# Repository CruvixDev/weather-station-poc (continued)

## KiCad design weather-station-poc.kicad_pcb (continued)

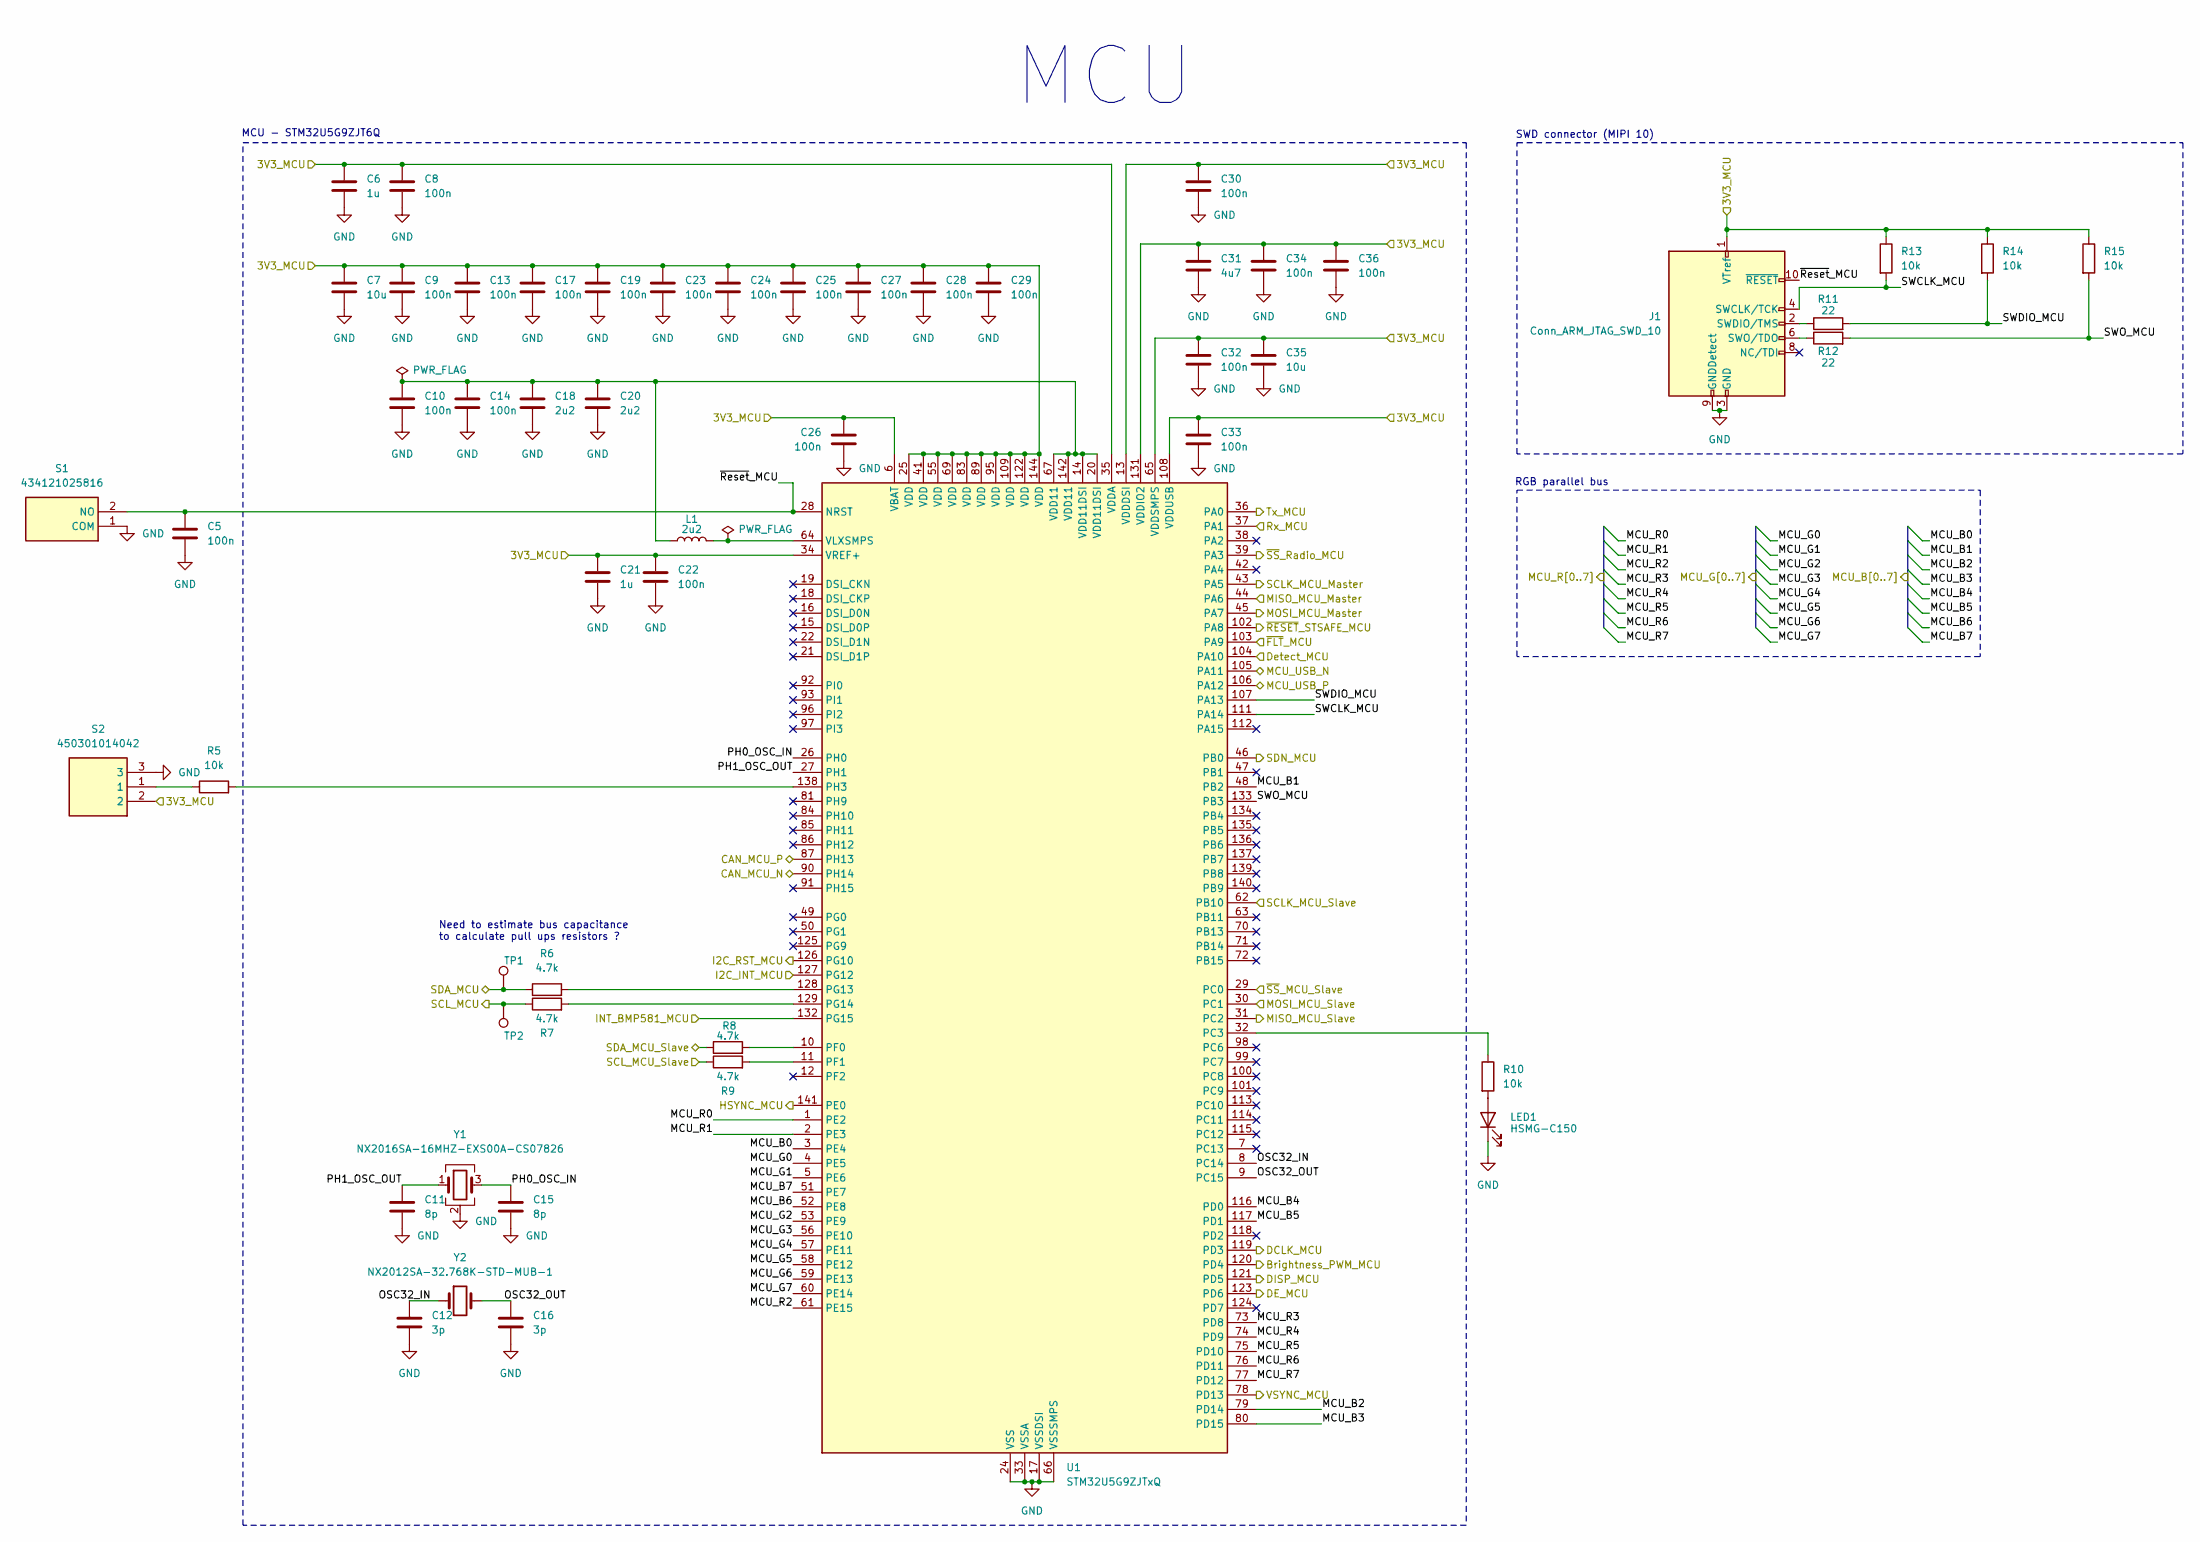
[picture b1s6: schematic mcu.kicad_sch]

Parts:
C5, C8, C9, C10, C13, C14, C17, C19, C22, C23, C24, C25, C26, C27, C28, C29, C30, C32, C33, C34, C36: 100n; C_0603_1608Metric_Pad1.08x0.95mm_HandSolder; Manufacturer_Part_Number 885012206020
C6, C21: 1u; C_0603_1608Metric_Pad1.08x0.95mm_HandSolder; Manufacturer_Part_Number 885012206026
C7, C35: 10u; C_0603_1608Metric_Pad1.08x0.95mm_HandSolder; Manufacturer_Part_Number GRM188Z71A106KA73D
C11, C15: 8p; C_0402_1005Metric_Pad0.74x0.62mm_HandSolder; Manufacturer_Part_Number CC0402CRNPO9BN8R2
C12, C16: 3p; C_0402_1005Metric_Pad0.74x0.62mm_HandSolder; Manufacturer_Part_Number CC0402BRNPO9BN3R3
C18, C20: 2u2; C_0603_1608Metric_Pad1.08x0.95mm_HandSolder; Manufacturer_Part_Number 885012206027
C31: 4u7; C_0603_1608Metric_Pad1.08x0.95mm_HandSolder; Manufacturer_Part_Number GRM188Z71A475KE15J
J1: Conn_ARM_JTAG_SWD_10; FTSH10501LDVK; Manufacturer_Part_Number FTSH-105-01-L-DV-K
L1: 2u2; L_0805_2012Metric_Pad1.05x1.20mm_HandSolder; Manufacturer_Part_Number LQM21PN2R2MGHL
LED1: HSMG-C150; LEDC3216X120N; Mouser Part Number 630-HSMG-C150
R5, R10, R13, R14, R15: 10k; R_0603_1608Metric_Pad0.98x0.95mm_HandSolder; Manufacturer_Part_Number 560112116005
R6, R7, R8, R9: 4.7k; R_0603_1608Metric_Pad0.98x0.95mm_HandSolder; Manufacturer_Part_Number 560112116006
R11, R12: 22; R_0603_1608Metric_Pad0.98x0.95mm_HandSolder; Manufacturer_Part_Number 560112116043
S1: 434121025816; 434121050816; Mouser Part Number 710-434121025816
S2: 450301014042; Mouser Part Number 710-450301014042
TP1, TP2: TestPoint; 5015; Manufacturer_Part_Number N/A
U1: STM32U5G9ZJTxQ; LQFP-144_20x20mm_P0.5mm; Manufacturer_Part_Number STM32U5G9ZJT6Q
Y1: NX2016SA-16MHZ-EXS00A-CS07826; NX2016SA16MHZEXS00ACS07826; Mouser Part Number 344-MHZEXS00ACS07826
Y2: NX2012SA-32.768K-STD-MUB-1; NX2012SA32768KSTDMUB1; Mouser Part Number 344-NX2012SA32768K1

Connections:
+3V3: C6.1, C7.1, C8.1, C9.1, C13.1, C17.1, C19.1, C21.1, C22.1, C23.1, C24.1, C25.1, C26.2, C27.1, C28.1, C29.1, C30.2, C31.1, C32.2, C33.1, C34.1, C35.1, C36.1, J1.1 (VTref), R13.1, R14.1, R15.1, S2.2, U1.6 (VBAT), U1.13 (VDDDSI), U1.25 (VDD), U1.34 (VREF+), U1.35 (VDDA), U1.41 (VDD), U1.55 (VDD), U1.65 (VDDSMPS), U1.69 (VDD), U1.83 (VDD), U1.89 (VDD), U1.95 (VDD), U1.108 (VDDUSB), U1.109 (VDD), U1.122 (VDD), U1.131 (VDDIO2), U1.144 (VDD); also elsewhere on the board
/debug/CAN_Debug_N: U1.90 (PH14); also elsewhere on the board
/debug/CAN_Debug_P: U1.87 (PH13); also elsewhere on the board
/debug/MISO_Debug: U1.31 (PC2); also elsewhere on the board
/debug/MOSI_Debug: U1.30 (PC1); also elsewhere on the board
/debug/Rx_Debug: U1.36 (PA0); also elsewhere on the board
/debug/SCLK_Debug: U1.62 (PB10); also elsewhere on the board
/debug/SCL_Debug: R9.1; also elsewhere on the board
/debug/SDA_Debug: R8.1; also elsewhere on the board
/debug/Tx_Debug: U1.37 (PA1); also elsewhere on the board
/debug/~SS_Debug: U1.29 (PC0); also elsewhere on the board
/lcd/DCLK_LCD: U1.119 (PD3); also elsewhere on the board
/lcd/DE_LCD: U1.123 (PD6); also elsewhere on the board
/lcd/DISP_LCD: U1.121 (PD5); also elsewhere on the board
/lcd/HSYNC_LCD: U1.141 (PE0); also elsewhere on the board
/lcd/I2C_INT_LCD: U1.127 (PG12); also elsewhere on the board
/lcd/I2C_RST_LCD: U1.126 (PG10); also elsewhere on the board
/lcd/LCD_B0: U1.3 (PE4); also elsewhere on the board
/lcd/LCD_B1: U1.48 (PB2); also elsewhere on the board
/lcd/LCD_B2: U1.79 (PD14); also elsewhere on the board
/lcd/LCD_B3: U1.80 (PD15); also elsewhere on the board
/lcd/LCD_B4: U1.116 (PD0); also elsewhere on the board
/lcd/LCD_B5: U1.117 (PD1); also elsewhere on the board
/lcd/LCD_B6: U1.52 (PE8); also elsewhere on the board
/lcd/LCD_B7: U1.51 (PE7); also elsewhere on the board
/lcd/LCD_G0: U1.4 (PE5); also elsewhere on the board
/lcd/LCD_G1: U1.5 (PE6); also elsewhere on the board
/lcd/LCD_G2: U1.53 (PE9); also elsewhere on the board
/lcd/LCD_G3: U1.56 (PE10); also elsewhere on the board
/lcd/LCD_G4: U1.57 (PE11); also elsewhere on the board
/lcd/LCD_G5: U1.58 (PE12); also elsewhere on the board
/lcd/LCD_G6: U1.59 (PE13); also elsewhere on the board
/lcd/LCD_G7: U1.60 (PE14); also elsewhere on the board
/lcd/LCD_R0: U1.1 (PE2); also elsewhere on the board
/lcd/LCD_R1: U1.2 (PE3); also elsewhere on the board
/lcd/LCD_R2: U1.61 (PE15); also elsewhere on the board
/lcd/LCD_R3: U1.73 (PD8); also elsewhere on the board
/lcd/LCD_R4: U1.74 (PD9); also elsewhere on the board
/lcd/LCD_R5: U1.75 (PD10); also elsewhere on the board
/lcd/LCD_R6: U1.76 (PD11); also elsewhere on the board
/lcd/LCD_R7: U1.77 (PD12); also elsewhere on the board
/lcd/SCL_LCD: R7.1, TP2.1 (1_1); also elsewhere on the board
/lcd/SDA_LCD: R6.1, TP1.1 (1_1); also elsewhere on the board
/lcd/VSYNC_LCD: U1.78 (PD13); also elsewhere on the board
/mcu/Brightness_PWM_MCU: U1.120 (PD4); also elsewhere on the board
/mcu/Detect_MCU: U1.104 (PA10); also elsewhere on the board
/mcu/INT_BMP581_MCU: U1.132 (PG15); also elsewhere on the board
/mcu/MCU_USB_N: U1.105 (PA11); also elsewhere on the board
/mcu/MCU_USB_P: U1.106 (PA12); also elsewhere on the board
/mcu/MISO_MCU_Master: U1.44 (PA6); also elsewhere on the board
/mcu/MOSI_MCU_Master: U1.45 (PA7); also elsewhere on the board
/mcu/OSC32_IN: C12.1, U1.8 (PC14), Y2.1
/mcu/OSC32_OUT: C16.1, U1.9 (PC15), Y2.2
/mcu/PH0_OSC_IN: C15.2, U1.26 (PH0), Y1.3
/mcu/PH1_OSC_OUT: C11.2, U1.27 (PH1), Y1.1
/mcu/SCLK_MCU_Master: U1.43 (PA5); also elsewhere on the board
/mcu/SDN_MCU: U1.46 (PB0); also elsewhere on the board
/mcu/SWCLK_MCU: J1.4 (SWCLK/TCK), R13.2, U1.111 (PA14)
/mcu/SWDIO_MCU: R11.2, R14.2, U1.107 (PA13)
/mcu/SWO_MCU: R12.2, R15.2, U1.133 (PB3)
/mcu/~FLT_MCU: U1.103 (PA9); also elsewhere on the board
/mcu/~RESET_STSAFE_MCU: U1.102 (PA8); also elsewhere on the board
/mcu/~Reset_MCU: C5.1, J1.10 (~RESET), S1.2 (NO), U1.28 (NRST)
/mcu/~SS_Radio_MCU: U1.39 (PA3); also elsewhere on the board
GND: C5.2, C6.2, C7.2, C8.2, C9.2, C10.2, C11.1, C12.2, C13.2, C14.2, C15.1, C16.2, C17.2, C18.2, C19.2, C20.2, C21.2, C22.2, C23.2, C24.2, C25.2, C26.1, C27.2, C28.2, C29.2, C30.1, C31.2, C32.1, C33.2, C34.2, C35.2, C36.2, J1.3 (GND), J1.5 (GND), J1.9 (GNDDetect), LED1.1 (K), S1.1 (COM), S2.3, U1.17 (VSSDSI), U1.23 (VSSDSI), U1.24 (VSS), U1.33 (VSSA), U1.40 (VSS), U1.54 (VSS), U1.66 (VSSSMPS), U1.68 (VSS), U1.82 (VSS), U1.88 (VSS), U1.94 (VSS), U1.110 (VSS), U1.130 (VSS), U1.143 (VSS), Y1.2 (G), Y1.4 (G); also elsewhere on the board
unnamed: C10.1, C14.1, C18.1, C20.1, L1.2, U1.14 (VDD11DSI), U1.20 (VDD11DSI), U1.67 (VDD11), U1.142 (VDD11)
unnamed: J1.2 (SWDIO/TMS), R11.1
unnamed: J1.6 (SWO/TDO), R12.1
unnamed: LED1.2 (A), R10.2
unnamed: R5.1, S2.1
unnamed: R10.1, U1.32 (PC3)
unnamed: R8.2, U1.10 (PF0)
unnamed: R9.2, U1.11 (PF1)
unnamed: R6.2, U1.128 (PG13)
unnamed: R7.2, U1.129 (PG14)
unnamed: R5.2, U1.138 (PH3)
unnamed: L1.1, U1.64 (VLXSMPS)

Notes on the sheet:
SWD connector (MIPI 10)
RGB parallel bus
Need to estimate bus capacitance to calculate pull ups resistors ?
MCU - STM32U5G9ZJT6Q
MCU

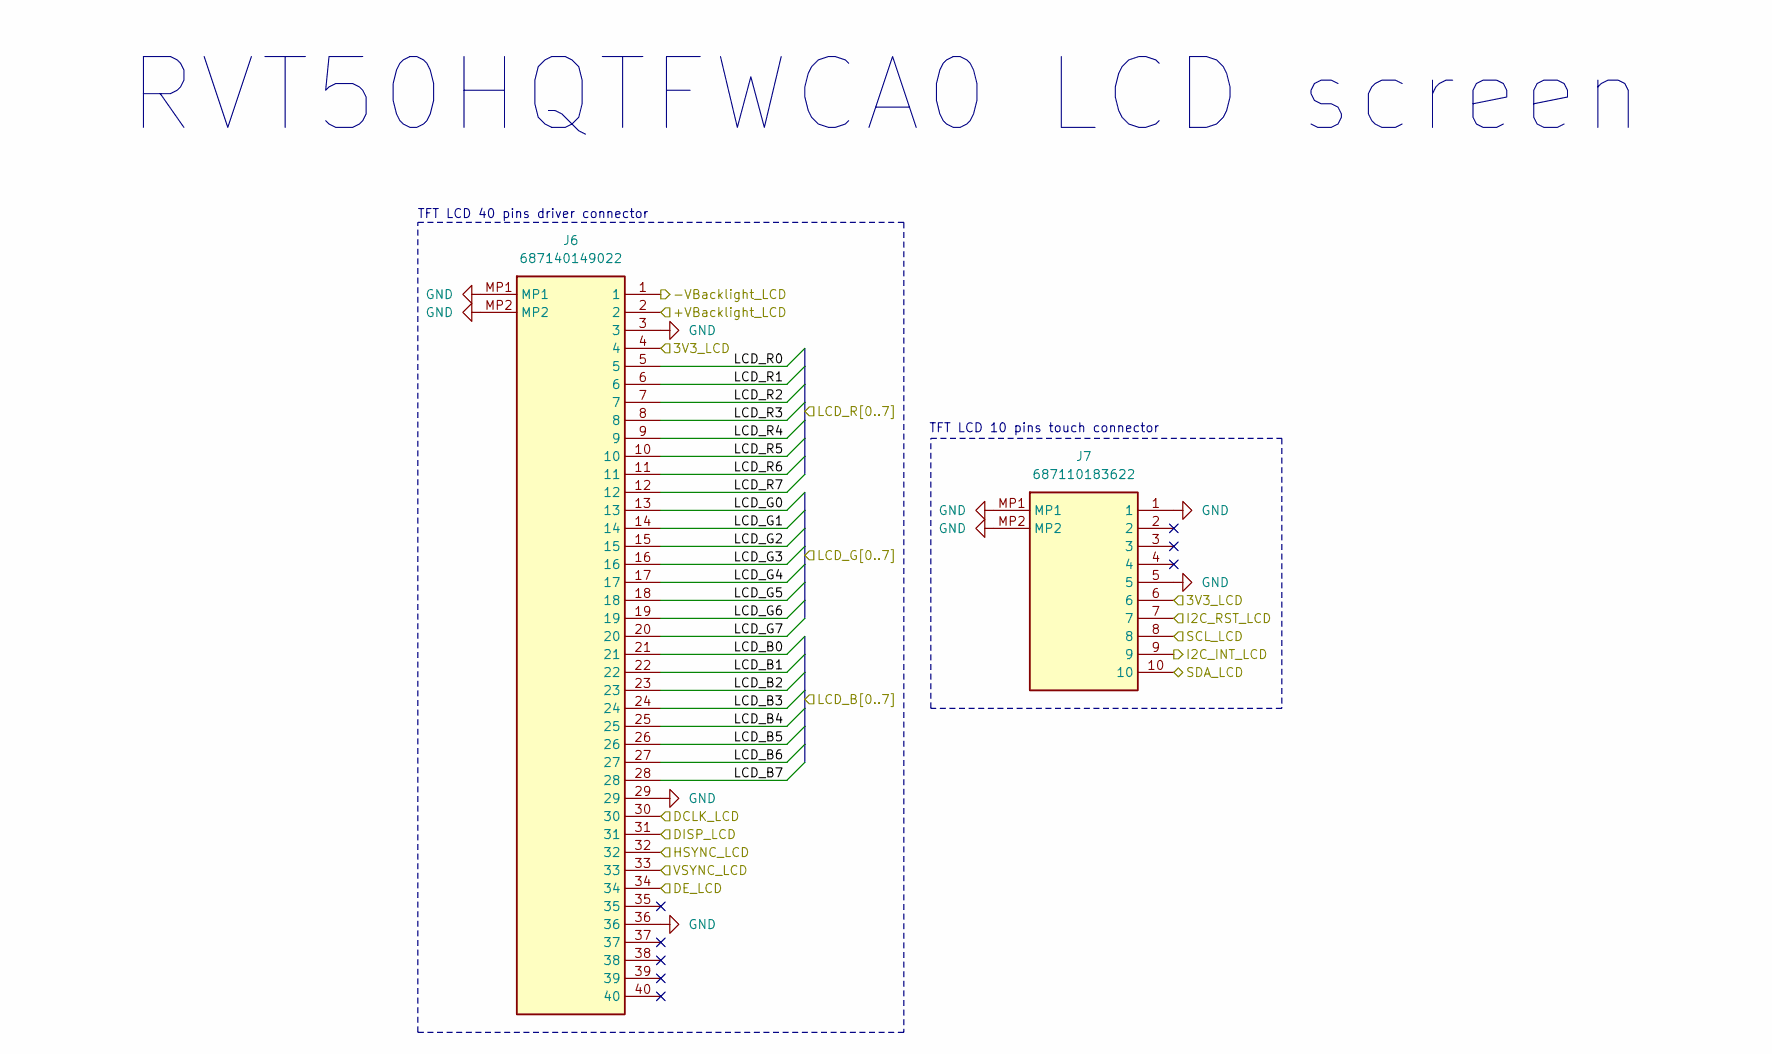
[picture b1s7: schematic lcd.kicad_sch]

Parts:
J6: 687140149022; Mouser Part Number 710-687140149022
J7: 687110183622; Mouser Part Number 710-687110183622

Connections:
+3V3: J6.4, J7.6; also elsewhere on the board
/lcd/+VBacklight_LCD: J6.2; also elsewhere on the board
/lcd/-VBacklight_LCD: J6.1; also elsewhere on the board
/lcd/DCLK_LCD: J6.30; also elsewhere on the board
/lcd/DE_LCD: J6.34; also elsewhere on the board
/lcd/DISP_LCD: J6.31; also elsewhere on the board
/lcd/HSYNC_LCD: J6.32; also elsewhere on the board
/lcd/I2C_INT_LCD: J7.9; also elsewhere on the board
/lcd/I2C_RST_LCD: J7.7; also elsewhere on the board
/lcd/LCD_B0: J6.21; also elsewhere on the board
/lcd/LCD_B1: J6.22; also elsewhere on the board
/lcd/LCD_B2: J6.23; also elsewhere on the board
/lcd/LCD_B3: J6.24; also elsewhere on the board
/lcd/LCD_B4: J6.25; also elsewhere on the board
/lcd/LCD_B5: J6.26; also elsewhere on the board
/lcd/LCD_B6: J6.27; also elsewhere on the board
/lcd/LCD_B7: J6.28; also elsewhere on the board
/lcd/LCD_G0: J6.13; also elsewhere on the board
/lcd/LCD_G1: J6.14; also elsewhere on the board
/lcd/LCD_G2: J6.15; also elsewhere on the board
/lcd/LCD_G3: J6.16; also elsewhere on the board
/lcd/LCD_G4: J6.17; also elsewhere on the board
/lcd/LCD_G5: J6.18; also elsewhere on the board
/lcd/LCD_G6: J6.19; also elsewhere on the board
/lcd/LCD_G7: J6.20; also elsewhere on the board
/lcd/LCD_R0: J6.5; also elsewhere on the board
/lcd/LCD_R1: J6.6; also elsewhere on the board
/lcd/LCD_R2: J6.7; also elsewhere on the board
/lcd/LCD_R3: J6.8; also elsewhere on the board
/lcd/LCD_R4: J6.9; also elsewhere on the board
/lcd/LCD_R5: J6.10; also elsewhere on the board
/lcd/LCD_R6: J6.11; also elsewhere on the board
/lcd/LCD_R7: J6.12; also elsewhere on the board
/lcd/SCL_LCD: J7.8; also elsewhere on the board
/lcd/SDA_LCD: J7.10; also elsewhere on the board
/lcd/VSYNC_LCD: J6.33; also elsewhere on the board
GND: J6.3, J6.29, J6.36, J6.MP1, J6.MP2, J7.1, J7.5, J7.MP1, J7.MP2; also elsewhere on the board

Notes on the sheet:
TFT LCD 40 pins driver connector
TFT LCD 10 pins touch connector
RVT50HQTFWCA0 LCD screen

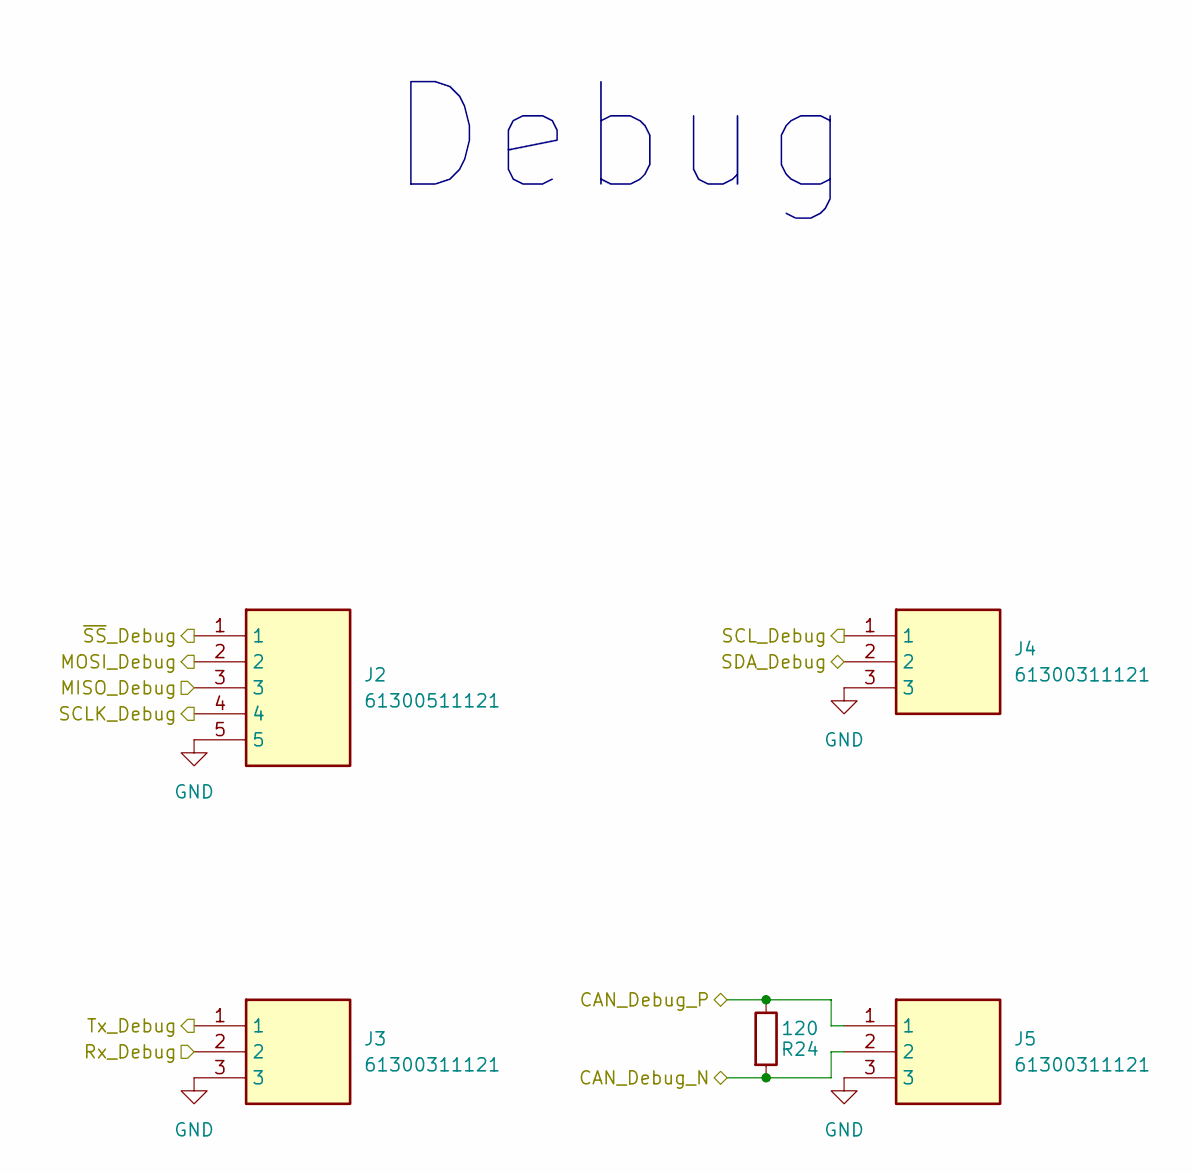
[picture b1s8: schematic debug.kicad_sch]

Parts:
J2: 61300511121; HDRV5W64P0X254_1X5_1270X254X854P; Mouser Part Number 710-61300511121
J3, J4, J5: 61300311121; HDRV3W64P0X254_1X3_762X254X869P; Mouser Part Number 710-61300311121
R24: 120; R_0603_1608Metric_Pad0.98x0.95mm_HandSolder; Manufacturer_Part_Number 560112116092

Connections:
/debug/CAN_Debug_N: J5.2, R24.2; also elsewhere on the board
/debug/CAN_Debug_P: J5.1, R24.1; also elsewhere on the board
/debug/MISO_Debug: J2.3; also elsewhere on the board
/debug/MOSI_Debug: J2.2; also elsewhere on the board
/debug/Rx_Debug: J3.2; also elsewhere on the board
/debug/SCLK_Debug: J2.4; also elsewhere on the board
/debug/SCL_Debug: J4.1; also elsewhere on the board
/debug/SDA_Debug: J4.2; also elsewhere on the board
/debug/Tx_Debug: J3.1; also elsewhere on the board
/debug/~SS_Debug: J2.1; also elsewhere on the board
GND: J2.5, J3.3, J4.3, J5.3; also elsewhere on the board

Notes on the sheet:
Debug

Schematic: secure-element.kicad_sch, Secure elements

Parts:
C78: 10u; C_0603_1608Metric_Pad1.08x0.95mm_HandSolder; Manufacturer_Part_Number GRM188Z71A106KA73D
C79: 100n; C_0603_1608Metric_Pad1.08x0.95mm_HandSolder; Manufacturer_Part_Number 885012206020
IC9: STSAFA110S8OCD03; SOIC127P600X175-8N; Mouser Part Number 511-STSAFA110S8OCD03

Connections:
+3V3: C78.1, C79.1, IC9.2 (VCC); also elsewhere on the board
/lcd/SCL_LCD: IC9.7 (SCL); also elsewhere on the board
/lcd/SDA_LCD: IC9.5 (SDA); also elsewhere on the board
/mcu/~RESET_STSAFE_MCU: IC9.1 (~RESET); also elsewhere on the board
GND: C78.2, C79.2, IC9.4 (GND); also elsewhere on the board

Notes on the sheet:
STSAFE-A110
Secure element (STSAFE)

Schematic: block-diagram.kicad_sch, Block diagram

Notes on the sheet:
JLCPCB stackup
L1 and L4 have a direct return paths through solid ground plane on L2 and L3. But Pwr on L1 is perhaps an issue in terms of EMC ?
3313 FR4 DK = 4.1 So 0.149mm trace width => 50.01 ohms For USB differentials pairs, 0.149mm trace width and 0.163mm spacing => 90.07 ohms (90 ohms +/- 10% for USB) Calculation according PCB way impedance calculator : ( https://www.pcbway.com/pcb_prototype/impedance_calculator.html )
PCB build up

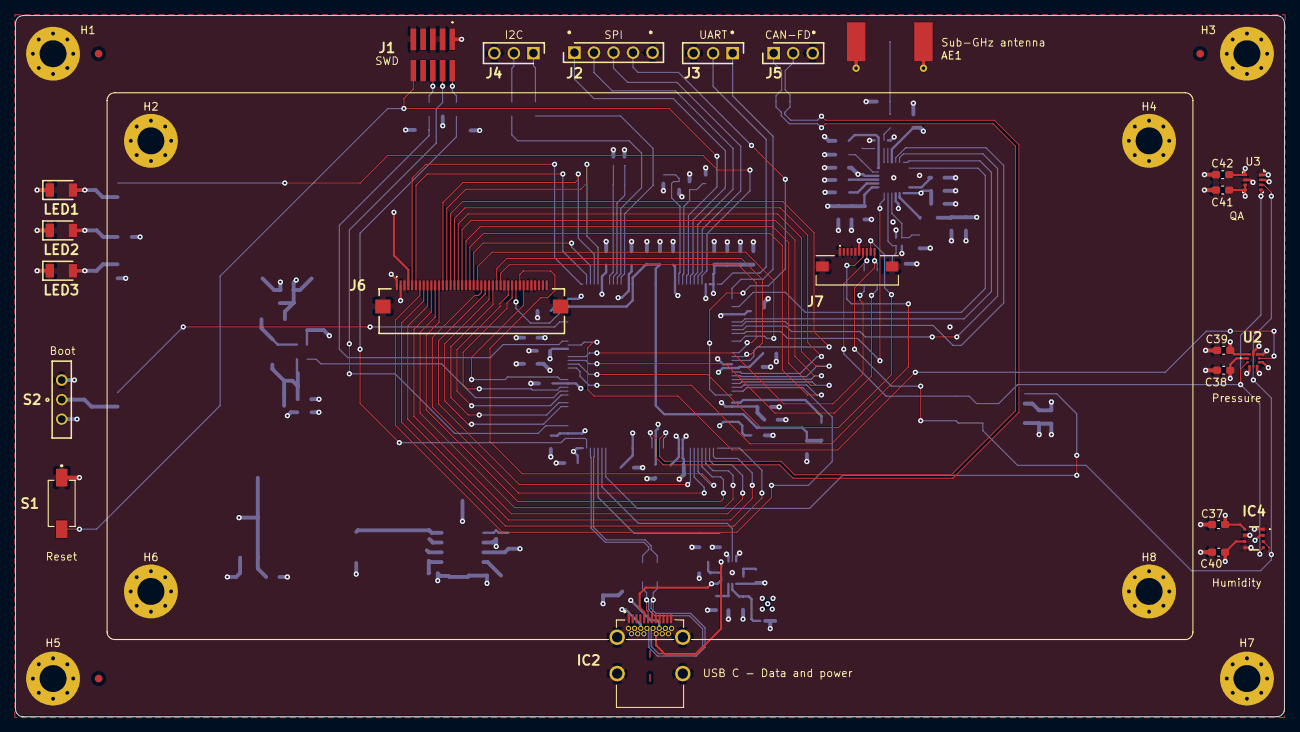
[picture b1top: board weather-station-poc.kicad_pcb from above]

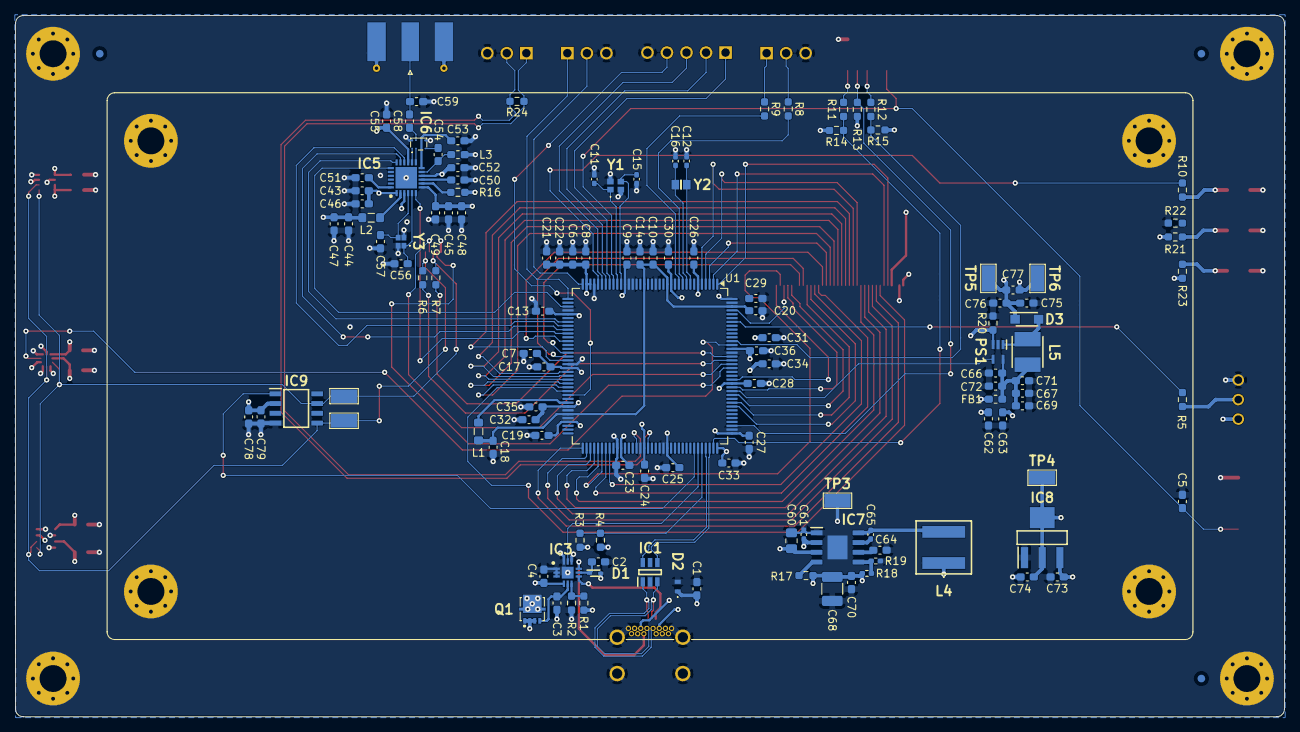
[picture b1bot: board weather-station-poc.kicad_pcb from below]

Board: 4 copper layers, 165.0 x 91.2 mm, 162 parts (129 on the bottom side), 112 nets.

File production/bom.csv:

Designator,Footprint,Quantity,Value,LCSC Part #
AE1,SMA_Molex_73251-1153_EdgeMount_Horizontal,1,Antenna,
"C1, C49, C52, C55, C58",0603,5,100p,
"C10, C13, C14, C17, C19, C2, C22, C23, C24, C25, C26, C27, C28, C29, C30, C32, C33, C34, C36, C37, C38, C39, C4, C41, C42, C5, C62, C66, C70, C72, C75, C77, C79, C8, C9",0603,35,100n,
"C11, C15",0402,2,8p,
"C12, C16",0402,2,3p,
"C18, C20",0603,2,2u2,
"C21, C47, C6, C64, C73",0603,5,1u,
"C3, C50",0603,2,470p,
"C31, C43, C74, C76",0603,4,4u7,
"C35, C63, C67, C69, C7, C71, C78",0603,7,10u,
C40,0603,1,220n,
"C44, C45, C46, C48, C51, C53, C54",0603,7,150n,
C56,0603,1,10p,
C57,0603,1,12p,
C59,0603,1,2p7,
"C60, L2",0805,2,10u,
C61,0402,1,220n,
C65,0402,1,100n,
C68,1210,1,100u,
D1,SODFL1608X70N,1,BAT54KFILM,
D2,ESDA25P351U1M,1,ESDA25P35-1U1M,
D3,SODFL3617X108N,1,SS26FL,
FB1,0603,1,70,
IC1,SOT95P280X145-6N,1,USBLC6-2SC6,
IC2,632723100011,1,632723100011,
IC3,QFN50P300X300X100-13N-D,1,TCPP01-M12,
IC4,BME690,1,BME690,
IC5,QFN50P400X400X100-25N-D,1,S2-LPQTR,
IC6,BALFSPI201D3,1,BALF-SPI2-01D3,
IC7,SOIC127P600X170-9N,1,LMR33640DDDAR,
IC8,SOT230P700X180-4N,1,LDL1117S33R,
IC9,SOIC127P600X175-8N,1,STSAFA110S8OCD03,
J1,FTSH10501LDVK,1,Conn_ARM_JTAG_SWD_10,
J2,HDRV5W64P0X254_1X5_1270X254X854P,1,61300511121,
"J3, J4, J5",HDRV3W64P0X254_1X3_762X254X869P,3,61300311121,
J6,687140149022,1,687140149022,
J7,687110183622,1,687110183622,
L1,0805,1,2u2,
L3,0603,1,12n,
L4,EXL1V06064R7R,1,4u7,
L5,INDPM4040X180N,1,10u,
"LED1, LED2, LED3",LEDC3216X120N,3,HSMG-C150,
PS1,SOT65P210X110-5N,1,TPS61169DCKR,
Q1,STL20N6F7,1,STL11N3LLH6,
"R1, R10, R13, R14, R15, R5",0603,6,10k,
"R11, R12",0603,2,22,
R16,0603,1,10,
R17,0603,1,100k,
R18,0402,1,100k,
R19,0402,1,37k4,
R2,0603,1,2k4,
R20,0603,1,1R5,
"R21, R23",0603,2,1k,
R22,0603,1,2k,
R24,0603,1,120,
R3,0603,1,110k,
R4,0603,1,200k,
"R6, R7, R8, R9",0603,4,4.7k,
S1,434121050816,1,434121025816,
S2,450301014042,1,450301014042,
"TP1, TP2, TP3, TP4, TP5, TP6",5015,6,TestPoint,
U1,LQFP-144_20x20mm_P0.5mm,1,STM32U5G9ZJTxQ,
U2,BMP581,1,BMP581,
U3,Bosch_LGA-8_2.5x2.5mm_P0.65mm_ClockwisePinNumbering,1,BME280,
Y1,NX2016SA16MHZEXS00ACS07826,1,NX2016SA-16MHZ-EXS00A-CS07826,
Y2,NX2012SA32768KSTDMUB1,1,NX2012SA-32.768K-STD-MUB-1,
Y3,NX1612SA50MEXS00ACS08403,1,NX1612SA-50M-EXS00A-CS08403,

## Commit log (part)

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2025-11-01 End of first phase USB C schematic
2025-11-01 Choose the right STM32 for the project Closes #3
2025-11-01 Add hierarchy sheets for project
2025-11-01 Add revision table into project
2025-11-01 Add block diagram in a sheet
2025-11-03 Test hierarchical labels on Kicad
2025-11-26 Beginning of all signals definition
2025-11-27 Add RGB 24 bits bus
2025-11-27 Define power flags
2025-11-30 Add WLED driver in power shcematic
2025-11-30 Add FPC/FFC connectors for LCD display screen
2025-11-30 Use local labels for RGB bus in folio and add title for all folio
2025-11-30 Clean up PCB for now
2025-11-30 Synchronise hierarchical pins for LCD
2025-12-01 Add external Ethernet PHY in SPI (limited to 10 Mbits/s)
2025-12-01 Add LCD signals to MCU and LCD folios
2025-12-01 Add SWG ARM/JTAG connector 10 pins
2025-12-03 Add debug connectors
2025-12-03 Cable all sensors
2025-12-03 Assign MCU pins
2025-12-06 Connect all pins to MCU
2025-12-06 Add crystal oscillator and button for reset
2025-12-06 Add LSE external clock for MCU
2025-12-06 Add S2LP schematic
2025-12-07 Fix some ERC errors
2025-12-07 Fix warnings for footprint
2025-12-07 Separate decoupling capacitors
2025-12-07 Modify symbols of LDO and S2LP
    Symbols for LDO and S2LP are inconsistent, because LDO VOUT pin was not in POWER OUTPUT type and S2LP wait for POWER INPUT on VDDS ... Moreover, decoupling capacitors on S2LP was a hell, because ERC 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
2025-12-07 Functionnal block delimiting in schematics
2025-12-07 Add status LED for MCU and power supplies
2025-12-10 Prepare Ethernet schematic (LAN8651)
2025-12-12 Finish ethernet schematic and add second LDO for wake/sleep of ETH
2025-12-12 Add STSAFE element
2025-12-14 Reorganise synoptic schematic for better reading Closes #26
2025-12-16 Fix errors in synoptic and hierarchic pins
2025-12-16 Fix error on SS SPI pin direction for debug
2025-12-16 Add decoupling capacitors for USB C power sink
2025-12-16 Add decouplings capacitor and check schematic
2025-12-16 Continue schematic review
2025-12-16 Add TODOs and update pdf schematic
2025-12-21 Fix some little warnings and refomat schematics files
2025-12-21 Replace sub d 9 connectors by pin headers for CAN
    Sub D 9 pts connectors are imposant on PCB
2025-12-21 Rename Ethernet schematic file
2025-12-21 Add reference for debug connectors (pin headers)
2025-12-21 Add RJ45 connector from Wurth
2025-12-21 Remove Ethernet part, critical error, LAN8651 is 10BASE-T1S !
    10BASE-T1S is not suitable with RJ45 connector and not connectable to computer
2025-12-21 Reorder components number
2025-12-22 Assign 0603 footprint to all capacitors
2025-12-22 Assign 0603 footprints to all resistors
2025-12-22 Create a BOM and update pdf schematic
2025-12-23 Setup crystal oscillators for MCU and S2LP
2025-12-23 Add switch reference form WE for boot selection mode
2025-12-23 Add a button reference for reset MCU
2025-12-24 Use preconised diodes for USB-C by ST
2025-12-24 Add SS26FL diode for LCD power supply
2025-12-24 Add Riverdi datasheet and AN into docs
2025-12-26 Homogenation of symbols
2025-12-26 Fill the cartridge for all schematics
2025-12-26 Replace coma by semicolon in BOM for Excel
2025-12-26 Add footprints for inductors, missing one for L6
2025-12-26 Components reindexing and update of PCB
2025-12-26 Add a new reference for L6 inductor on boost converter
2025-12-26 Update PCB layout and remove unused PDF
    Deleted the unused DS_RVT50HQTFWCA0_Rev.1.0 (1).pdf from docs. Updated weather-station-poc.kicad_pcb with significant component repositioning, including capacitors, resistors, ICs, LEDs, connectors, 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
2025-12-27 Prepare PCB size with mounting holes
2025-12-30 Use 4 layers board
2026-01-02 LCD 10 pins connector is top and not bottom face, replace connector part
2026-01-03 Place MCU and its components around
2026-01-03 Place power supplies components and STSAFE
2026-01-03 Place S2LP radio module on PCB
2026-01-03 Place PCB top components
2026-01-03 All components placed on PCB
2026-01-04 Add ferrite bead part number in power schematic
2026-01-04 Add 3D models to some components and move JTAG connector
2026-01-11 Remove L5 inductos on radio oscillator
2026-01-11 Simplify S2LP schematic based on datasheet
2026-01-12 Place 4 others hole on the border of the PCB, TODO: place its correctly
2026-01-13 Improve components placement with a bigger grid
2026-01-17 Place all components on the PCB correctly
2026-01-18 Align all components on PCB to have a good design
2026-01-18 Remove C50 and C56 duplicates
2026-01-20 Use default stack up from PCB Way and enable controled impedance option
2026-01-20 Specify FR4 as prepreg material
2026-01-21 Bad placement of serigraphy on bottom for some components
2026-01-25 Place J6 and J7 FFC connector to take in account spacer height
2026-02-01 Modify USB data signals name to trace diff pairs
2026-02-01 Add mounting holes with pads in schematic and place it into pcb
2026-02-01 Use I2C for slave MCU for bootloader
2026-02-02 Add net class and their colors to ease PCB routing
2026-02-19 Use SMA coaxial connector for antenna, PCB antenna later
2026-02-22 Prepare PCB for routing
2026-02-23 Place all vias for GND and add fiducials on top and bottom
2026-02-24 Refactor Sub-GHz part to ease SPI routing
2026-03-08 End of LCD routing
2026-03-23 End of communication protocols routing
2026-03-24 Clean routing
2026-03-25 Add polygon pour for 5V power supply
2026-03-28 Add 3V3 copper pour on L1 and connect to nets
2026-03-29 Update schematic to Kicad 10
2026-03-29 End of routing and DRC rules check fix
2026-03-29 Improve 3.3V copper pour fill near USB
2026-03-29 Use green PCB instead of black, as the proto probably would not work
2026-03-30 Add serigraphy to identify GND on HE14 pins headers
2026-04-01 Improve CC1 via placement
2026-04-03 Add tests points with 5015 footprint for practicity
2026-04-03 Do no mount antenna coaxial antenna, to be soldered after by hand
2026-04-03 Choose ENIG finition for the PCB
2026-04-06 Add pull ups resistors for I2C bus and reformat some schematic files
2026-04-07 Add transfer vias for L1 to L4 transition
2026-04-10 Complete all references for components
    Modifgy Y1 and Y2 capacitors footprint from 0603 to 0402
    Modify footprint of SWD connector
2026-04-11 End of BOM
2026-04-11 Update CSV BOM for PCBWay
2026-04-11 Update PCB 3D png for documentation in readme
2026-04-14 Use JLCPCB standard stackup and so modify trace width for 50 ohm and 90 ohm diff
2026-04-14 Use protel for JLCPCB
2026-04-18 Modify reference for 8p and 3p capacitors
2026-04-19 Create BOM in JLCPCB format and create CPL file
2026-04-19 Ignore kicad_prl file
2026-05-01 Update block diagram
2026-05-01 Set I2C address for BMP sensors and document address
2026-05-01 Add all 3D models locally to project
2026-05-01 Use local 3D model for components
2026-05-17 Add some interesting links in the docs
2026-06-25 Rename sub-sheets for more consistency
